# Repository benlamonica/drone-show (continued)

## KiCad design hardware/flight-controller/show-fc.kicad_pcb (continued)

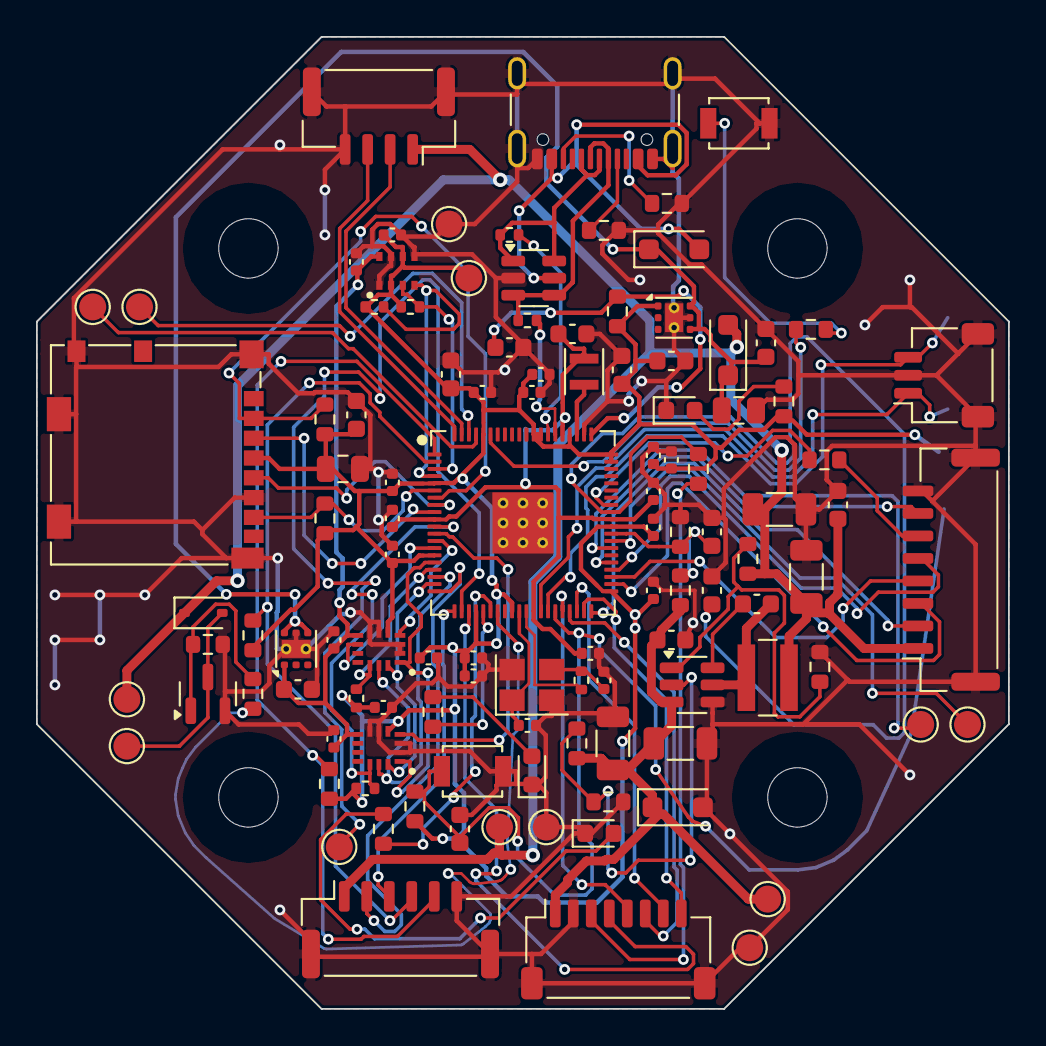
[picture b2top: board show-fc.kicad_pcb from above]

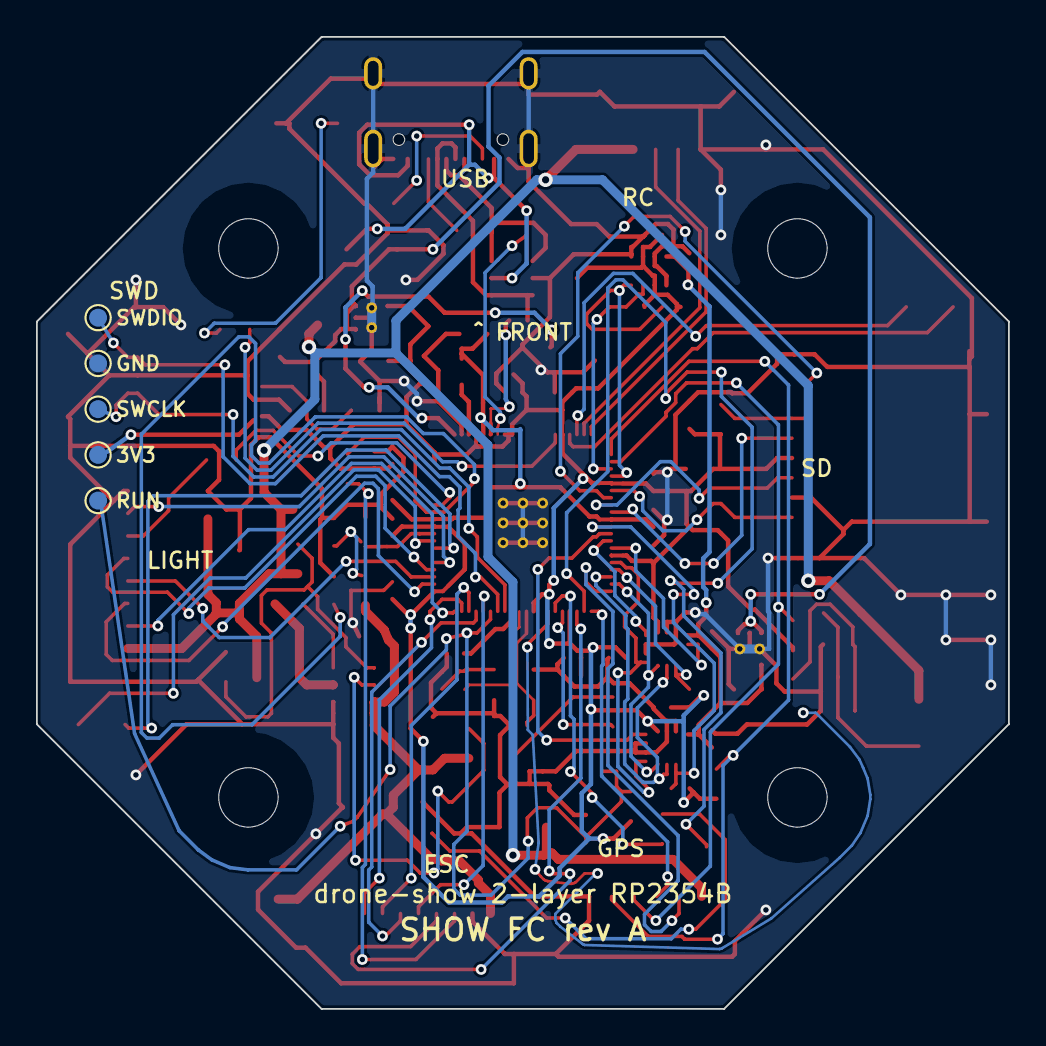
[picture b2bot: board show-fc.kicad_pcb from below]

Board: 2 copper layers, 54.0 x 54.0 mm, 121 parts (5 on the bottom side), 76 nets.

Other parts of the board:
TP14: SWDIO; TestPoint_Pad_D1.0mm
TP15: GND; TestPoint_Pad_D1.0mm
TP16: SWCLK; TestPoint_Pad_D1.0mm
TP17: +3V3; TestPoint_Pad_D1.0mm
TP18: RUN; TestPoint_Pad_D1.0mm

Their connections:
+3V3: TP17.1; also elsewhere on the board
GND: TP15.1; also elsewhere on the board
RUN: TP18.1; also elsewhere on the board
SWCLK: TP16.1; also elsewhere on the board
SWDIO: TP14.1; also elsewhere on the board

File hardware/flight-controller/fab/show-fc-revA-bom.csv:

Item #,Designator,Qty,Manufacturer,Mfg Part #,Description / Value,Package/Footprint,Type,LCSC,Your Instructions / Notes
1,U1,1,Raspberry Pi,RP2354B,RP2354B,QFN-80-1EP_10x10mm_P0.4mm_EP3.4x3.4mm,SMD,C39843328,
2,"C1,C2,C3,C4,C5,C6,C7,C8,C9,C10,C11,C15,C16,C17,C37,C38,C39,C40,C41,C42",20,Murata,GRM155R71C104KA88D,100n,C_0402_1005Metric,SMD,,
3,L1,1,Abracon,AOTA-B201610S3R3-101-T,3.3uH,L_Murata_DFE201610P,SMD,,RP2350 datasheet part; the dot (pin 1) goes to VREG_LX
4,"C12,C13,C14,C18,C30,C31",6,Murata,GRM188R61A475KE15D,4.7u,C_0603_1608Metric,SMD,,
5,R1,1,Yageo,RC0603FR-0733L,33,R_0603_1608Metric,SMD,,
6,Y1,1,Abracon,ABM8-272-T3,12MHz,Crystal_SMD_3225-4Pin_3.2x2.5mm,SMD,C20625731,
7,R2,1,Yageo,RC0402FR-071KL,1k,R_0402_1005Metric,SMD,,
8,"C19,C20",2,Murata,GRM1555C1H150JA01D,15p,C_0402_1005Metric,SMD,,
9,SW1,1,Omron,B3U-1000P,BOOT,SW_SPST_B3U-1000P,SMD,,
10,"R3,R5,R6,R15,R18",5,Yageo,RC0603FR-071KL,1k,R_0603_1608Metric,SMD,,
11,SW2,1,Omron,B3U-1000P,RESET,SW_SPST_B3U-1000P,SMD,,
12,"R4,R17,R26,R27",4,Yageo,RC0603FR-0710KL,10k,R_0603_1608Metric,SMD,,
13,"C21,C25,C28,C33,C34,C44",6,Murata,GCM188R71H104KA57D,100n,C_0603_1608Metric,SMD,,
14,J8,1,JST,SM03B-SRSS-TB(LF)(SN),SWD,JST_SH_SM03B-SRSS-TB_1x03-1MP_P1.00mm_Horizontal,SMD,,
15,D1,1,Wurth Elektronik,150060BS75000,LED blue,LED_0603_1608Metric,SMD,,
16,D2,1,Wurth Elektronik,150060VS75000,LED green,LED_0603_1608Metric,SMD,,
17,J1,1,GCT,USB4105-GF-A,USB-C,USB_C_Receptacle_GCT_USB4105-xx-A_16P_TopMnt_Horizontal,SMD,,
18,"R7,R8",2,Yageo,RC0603FR-075R1KL,5.1k,R_0603_1608Metric,SMD,,
19,"R9,R10",2,Yageo,RC0402FR-0727L,27,R_0402_1005Metric,SMD,,
20,U2,1,STMicroelectronics,USBLC6-2SC6,USBLC6-2SC6,SOT-23-6,SMD,,
21,D3,1,Littelfuse,SMF30A,SMF30A,D_SOD-123F,SMD,,"unidirectional; cathode (pad 1) on VBAT, clamps ESC spikes below the buck's 60 V rating"
22,"C22,C23",2,Murata,GRM31CR61H106KA12L,10u 50V,C_1206_3216Metric,SMD,,
23,C24,1,Murata,GCM188R71H104KA57D,100n 50V,C_0603_1608Metric,SMD,,
24,U3,1,Texas Instruments,LMR51635YDDCR,LMR51635YDDCR,SOT-23-6,SMD,C45262770,
25,"R11,R16,R35",3,Yageo,RC0603FR-07100KL,100k,R_0603_1608Metric,SMD,,
26,R12,1,Yageo,RC0603FR-0714KL,14k,R_0603_1608Metric,SMD,,
27,L2,1,Wurth Elektronik,74438357047,4.7uH,L_Wuerth_MAPI-4020,SMD,,
28,R13,1,Yageo,RC0603FR-0753R6KL,53.6k,R_0603_1608Metric,SMD,,
29,R14,1,Yageo,RC0603FR-0710R2KL,10.2k,R_0603_1608Metric,SMD,,
30,"C26,C27",2,Murata,GRM31CR61E226KE15L,22u 25V,C_1206_3216Metric,SMD,,
31,"D4,D5",2,Nexperia,"PMEG3020EH,115",PMEG3020EH,D_SOD-123F,SMD,,
32,"C29,C43",2,Murata,GRM21BR61C106KE15L,10u,C_0805_2012Metric,SMD,,
33,U4,1,Texas Instruments,LP5912-3.3DRVR,LP5912-3.3DRVR,WSON-6-1EP_2x2mm_P0.65mm_EP1x1.6mm_ThermalVias,SMD,C524780,
34,U5,1,Texas Instruments,LP5912-1.8DRVR,LP5912-1.8DRVR,WSON-6-1EP_2x2mm_P0.65mm_EP1x1.6mm_ThermalVias,SMD,C2876234,clean supply for the IMU and barometer cores
35,C32,1,Murata,GRM188R61E105KA12D,1u,C_0603_1608Metric,SMD,,
36,D6,1,Wurth Elektronik,150060RS75000,LED red,LED_0603_1608Metric,SMD,,
37,U6,1,TDK InvenSense,ICM-42688-P,ICM-42688-P,LGA-14_3x2.5mm_P0.5mm,SMD,,"IMU1; pin 9 is CLKIN, driven by a 32 kHz PWM from GPIO15"
38,U7,1,Bosch Sensortec,BMI270,BMI270,LGA-14_3x2.5mm_P0.5mm,SMD,C2836813,"IMU2, different vendor for redundancy"
39,"R22,R23",2,Yageo,RC0402FR-0710KL,10k,R_0402_1005Metric,SMD,,
40,U8,1,Infineon,DPS368XTSA1,DPS368,Infineon_VLGA-8_2.0x2.5mm_P0.65mm,SMD,,"I2C address 0x76 (SDO low), CSB high selects I2C. Cover with open-cell foam."
41,"R24,R25",2,Yageo,RC0402FR-072R2KL,2.2k,R_0402_1005Metric,SMD,,
42,J2,1,Molex,1040310811,microSD,microSD_HC_Molex_104031-0811,SMD,,
43,J3,1,JST,SM08B-SRSS-TB(LF)(SN),ESC,JST_SH_SM08B-SRSS-TB_1x08-1MP_P1.00mm_Horizontal,SMD,C160407,"Betaflight standard ESC pinout, same as OpenFC-Lite P1"
44,J4,1,JST,SM06B-GHS-TB(LF)(SN),GPS,JST_GH_SM06B-GHS-TB_1x06-1MP_P1.25mm_Horizontal,SMD,,Pixhawk GPS1 pinout: RTK board with compass
45,J5,1,JST,SM08B-GHS-TB(LF)(SN),LIGHT,JST_GH_SM08B-GHS-TB_1x08-1MP_P1.25mm_Horizontal,SMD,,"light / Wi-Fi board: MAVLink UART with flow control, LED data, GPIO"
46,J6,1,JST,SM04B-GHS-TB(LF)(SN),RC,JST_GH_SM04B-GHS-TB_1x04-1MP_P1.25mm_Horizontal,SMD,,CRSF / SBUS receiver for the safety pilot
47,R31,1,Yageo,RC0603FR-0747L,47,R_0603_1608Metric,SMD,,
48,"R32,R33",2,Yageo,RC0603FR-072R2KL,2.2k,R_0603_1608Metric,SMD,,
49,Q1,1,onsemi,2N7002LT1G,2N7002,SOT-23,SMD,,
50,R34,1,Yageo,RC0603FR-07100L,100,R_0603_1608Metric,SMD,,
51,D7,1,onsemi,1N4148WS,1N4148WS,D_SOD-323,SMD,,

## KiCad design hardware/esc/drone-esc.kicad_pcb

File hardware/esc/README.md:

# drone-esc: 4-layer 4-in-1 ESC for the show drones

A 4-layer re-layout of [OpenESC-30x30](https://github.com/benlamonica/OpenESC-30x30)
for PCBWay's standard process. The circuit is the prototype's (four AT32F421
MCUs running AM32, four NSG2065Q gate drivers, 24 SP40N01GHNK FETs, INA186
current sense, LMR54406 10 V buck, TLV767 3.3 V LDO). What changed is the
board: 4 layers instead of 6, 0402 and bigger passives, and an 80 mm octagon
instead of a 30 x 30 mm square.

## Status

The board is placed and routed. KiCad DRC shows 0 errors and 0 unconnected
items. The remaining warnings are expected: schematic parity for U3 pins 3 to
11 (the FC wire pads were taken off the board, and J1 carries those signals),
the schematic's empty LCSC fields, and a few dangling stubs and thin pour
slivers. Look over the gate drive and current-sense routing before ordering a
big batch. Nobody has built one yet.

## Ratings

| | |
|---|---|
| Battery | 4S to 6S (25.2 V max). The FETs are 40 V parts, so leave the prototype's 6S ceiling alone. |
| Current | about 35 A continuous per motor with airflow, limited by 2 oz copper and the FET package. Show flying (hover plus gentle moves) needs a fraction of that. |
| Firmware | AM32 for AT32F421, same pinout as OpenESC-30x30, flashed over the motor signal lines through J1 (AM32 bootloader), or over SWD test points. |
| FC link | JST-SH 8-pin side entry, SM08B-SRSS-TB (Betaflight 4-in-1 order: VBAT, GND, CURR, TLM, M1 to M4; TLM is not connected). |
| Mounting | 30.5 mm M3 pattern, 3.3 mm unplated holes with a 6.9 mm copper-free ring, so it stacks with the FC on rubber standoffs. |

## Board

* 80 mm across the flats, octagonal, 1.6 mm FR4, 4 layers: 2 oz outer,
  1 oz inner. Layer 2 is a solid GND plane; layer 3 is a +BATT pour that a
  few signal tracks also cross.
* Two layers were tried first and did not work: at 66 mm the gate-drive lines
  had no room, and at 74 mm the routing cut the GND pour into islands, which
  is no good on a board switching 100+ A. The inner planes fix both and give a
  much shorter commutation loop.
* Each motor owns one edge. The high-side FET of each half-bridge is on top,
  its low-side FET directly underneath on the bottom, and the phase copper runs
  out to plated motor pads on the edge.
* The outer layers are +BATT pour on top and GND pour on the bottom, stitched
  to the inner planes.
* The motor channels own the four axis edges; the corner flats carry the
  connections:
  * **Battery** on the rear-right corner flat (marked BAT+ / BAT- on both
    sides). Each pad is a 7 x 6 mm plated pad with bare copper on both sides,
    a 2.2 mm hole (12 or 14 AWG goes straight through) and a ring of eight
    small plated holes so the current reaches both sides. Solder the battery
    lead on one side and the low-ESR electrolytic (35 V, 470 uF or more) on
    the other, legs on the matching pads, so the cap sits right at the power
    entry. The two current-sense shunts sit right beside BAT+, with the INA186
    and its input filter underneath on the bottom. Its output filter (R73,
    C94) is at the FC end, under J1.
  * **FC connector** J1 on the front-left corner flat: a side-entry JST SH
    with its opening facing out of the board edge, so the lead leaves sideways
    instead of standing up into the stack.
* Each channel's logic sits on the bottom, on the GND pour, in the wedge
  between the board centre and its FETs. The gate driver is just inboard of
  the FETs, with the gate resistors and bootstrap caps. The MCU is on the
  centre side of the driver, 6 mm from the middle of the board, so the six
  PWM lines are a few millimetres long and stay on one layer. The four MCUs
  form a ring round the centre, with their DShot resistors in the middle.
  The MCU's NRST, BOOT0 and VDDA parts, its 3V3 decoupling cap and the SWD
  test points are on top, right over it. The corners stay free for the
  battery, the FC connector and the 10 V / 3.3 V supplies, which are on the
  bottom of the rear-left corner.
* The MCU and gate-driver pins are 0.4 and 0.5 mm apart and boxed in on
  every side, which neither router gets out of reliably. So the MCU, the
  driver and the caps round them are placed exactly, and the escapes are
  drawn by `tools/route_prep.py`, the same in every channel: the PWM lines,
  the 3V3, NRST, VDDA and back-EMF escapes, and the driver's high-side row.
  The high-side gate lines drop to vias there and cross on top. 0.18 mm
  tracks keep every gap at 0.22 mm or more.
* 24 x 10 uF 1206 ceramics sit around the power path, next to each channel's
  high-side FETs.
* Parts: the MCU passives (decoupling, NRST, BOOT0, VDDA, back-EMF dividers,
  DShot resistor) are 0402, which gives the MCU room for a clear ring of
  escape tracks; everything else is 0603 or bigger. Nothing is smaller than
  0402. The ICs are the prototype's packages; the MCU QFN at 0.4 mm pitch is
  the finest pitch on the board.

### Changes from the prototype BOM

* The prototype's 0201 and 0402 resistors and capacitors became 0402 round
  each MCU (YAGEO RC0402, Samsung CL05B104KB5NNNC) and 0603 everywhere else
  (YAGEO RC0603, Samsung CL10). Same values throughout.
* J1 is the side-entry SM08B-SRSS-TB instead of a top-entry connector.
* The bulk ceramics are now real schematic symbols (C100 to C123) so they are
  in the BOM and the pick-and-place file.
* QFN-28 footprint: the prototype's footprint was missing pads 8, 23 and 24.
  They are back, so every MCU pin is soldered.

## Making it at PCBWay

Upload `fab/drone-esc-gerbers.zip` and choose:

| Option | Value |
|---|---|
| Layers | 4 |
| Material / thickness | FR-4 TG150, 1.6 mm |
| Copper | 2 oz outer, 1 oz inner |
| Min track / space | 7 / 8 mil (0.178 / 0.2 mm) |
| Min hole / via | 0.3 mm drill, 0.66 mm via pad (7 mil ring) |
| Surface finish | ENIG (flat pads for the QFNs) or lead-free HASL |
| Solder mask / silk | any colour |

For assembly upload `fab/drone-esc-bom.csv` and `fab/drone-esc-cpl.csv`.
Parts are on both sides. The design rules PCBWay checks against are in
`drone-esc.kicad_pro` and `drone-esc.kicad_dru`; open the board in KiCad 10 and
run DRC to see them.

## Frame changes this board needs

The board is bigger than the 30x30 prototype, so `frame/frame.py` needs:

* `BODY` 90 to about 110 mm, so the arm sockets clear the board's corner
  flats (37.8 mm from the centre).
* `GPS_MAST_R` 38 to about 53 mm, so the GPS mast clears the board edge
  (40 mm from the centre).
* Check both against the 3D model; they are worked out from the board outline,
  not test-fitted.
* Bottom-side parts stand about 1.2 mm proud of the board. The low ring and
  spokes at boss height in the hub touch them, so either raise the ESC on
  3 mm spacers/grommets or drop the ring by 3 mm.
* The battery leads leave from the rear-right corner flat, where motor 1's arm
  socket is. Leave a gap or notch in the hub wall there for the leads and the
  electrolytic (about 12 mm wide for two 12 AWG leads, more if the cap lies
  beside them), and route the leads back past the arm. The hub floor no longer
  needs a window under the board.
* J1's plug comes out of the front-left corner flat, sideways: leave about
  8 mm clear outside that flat (motor 4's arm socket) for the plug and its
  lead, which then runs up to the FC.

## Notes and limits

* Apart from the drawn escapes, the signal tracks are routed in three steps.
  First `tools/rescue_route.py`, a small grid maze router, routes the MCU's
  short local nets, the bootstrap nets and 3V3 on the near-empty board. Then
  Freerouting routes everything else round them. Finally the maze router
  finishes what Freerouting left open.
* RS2205-class motors are usually wound for 4S. On 6S pick a lower KV
  (about 1700 to 1900 KV) or limit throttle in the FC.
* The FETs and gate drivers sit on both sides, so the board can't be all
  parts-on-top like the FC. Bottom parts stand about 1.2 mm proud; the rubber
  standoffs between stacked boards need to be taller than that. Nothing on the
  board stands up into the stack any more: J1 is side entry and the
  electrolytic hangs off the battery pads.
* Four layers is a bit more per board than two at PCBWay, but still far below
  the prototype's six.

## Rebuilding

Everything is generated by scripts in `tools/` with KiCad 10:

```sh
FREEROUTING=/path/to/freerouting-1.9.0.jar PYTHON=/path/to/venv/bin/python sh tools/build.sh
sh tools/export.sh                                             # board -> fab/
```

A full build takes about 25 minutes on a laptop. `PYTHON` is a plain Python 3 with sexpdata, numpy, scipy and Pillow (the
netlist converter and the rescue router run there); the board scripts run in
KiCad's own Python (`KIPY`, found by itself on macOS). `sh tools/build.sh
place` stops after placement, which takes seconds, for trying placement
changes before a full routing run.

`tools/layout.py` holds the board geometry (size, FET positions, pads) that
the footprint and placement scripts share.

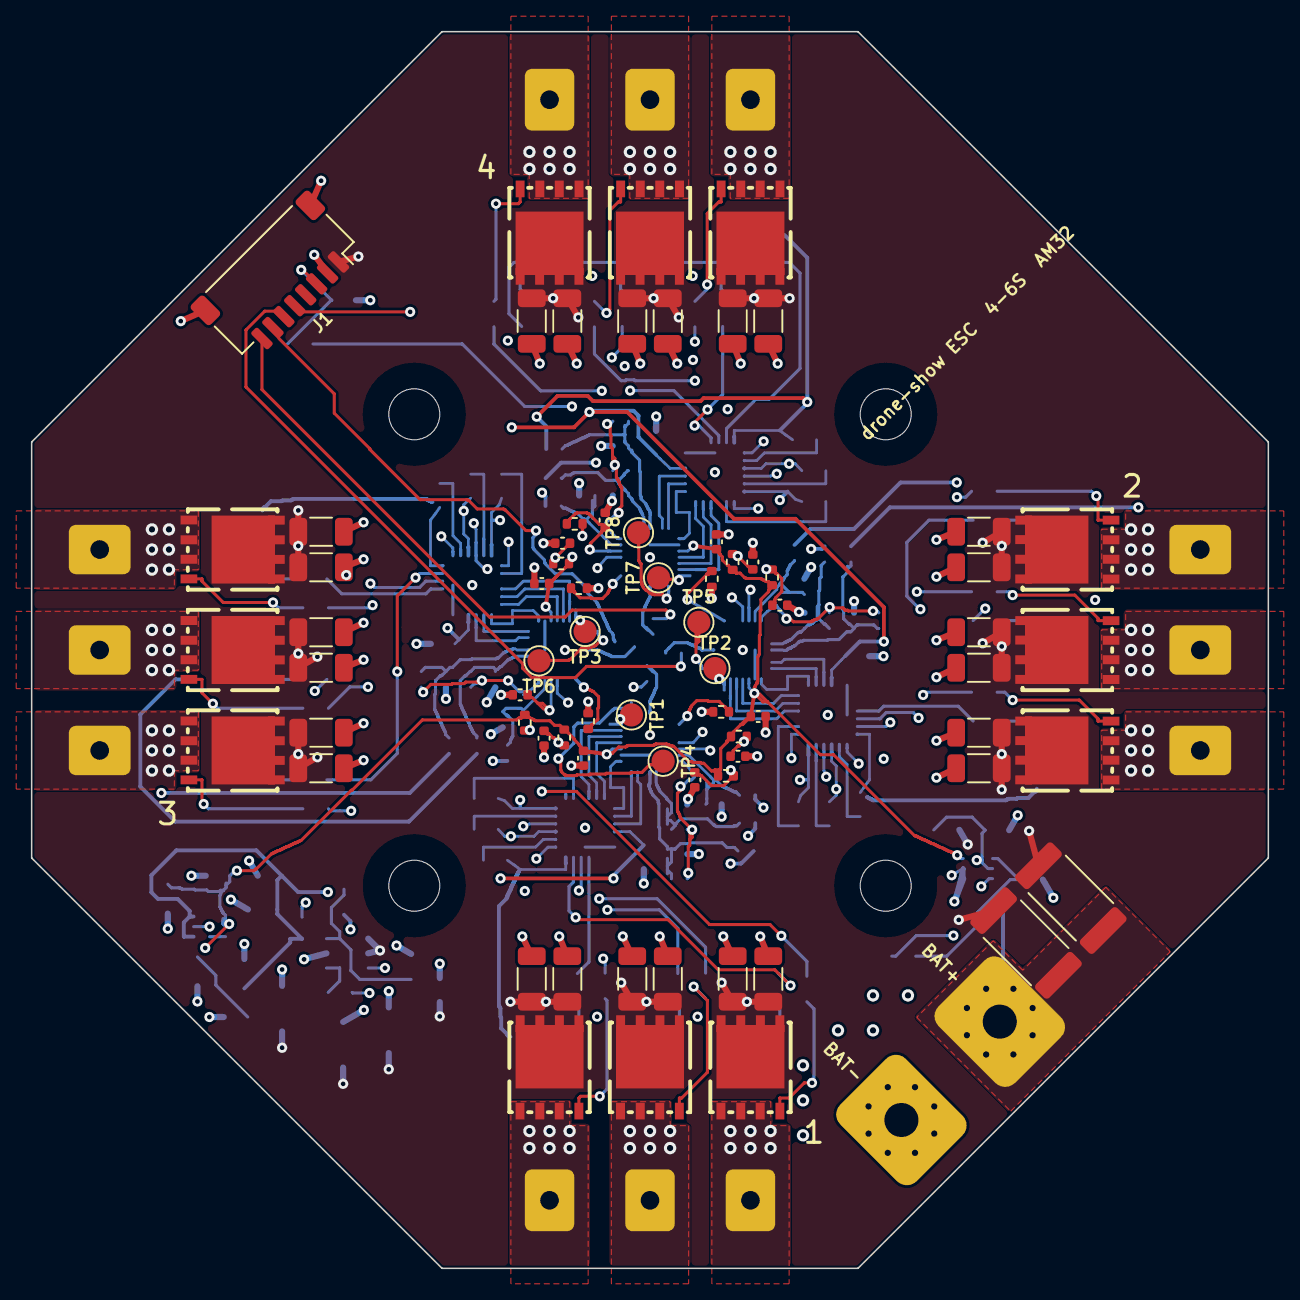
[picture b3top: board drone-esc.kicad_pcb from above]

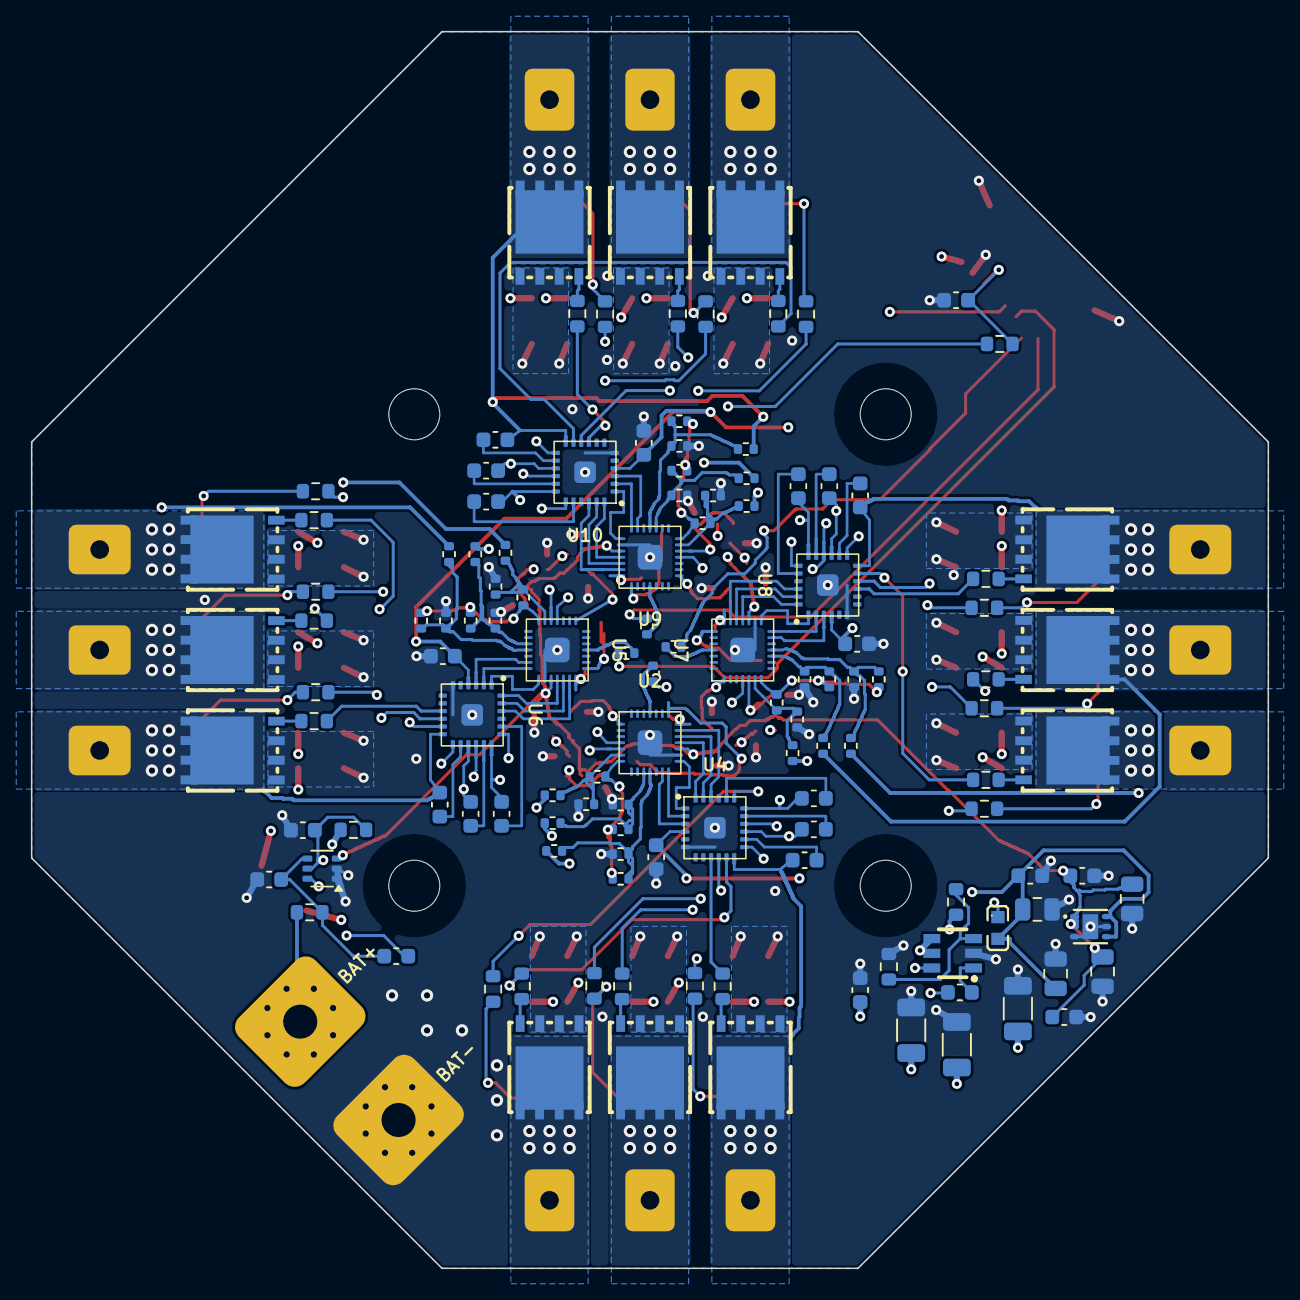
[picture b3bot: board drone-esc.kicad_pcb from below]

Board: 4 copper layers, 80.0 x 80.0 mm, 197 parts (125 on the bottom side), 152 nets.

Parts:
C2, C3, C6: 4.7uF; C_1206_3216Metric
C4, C47, C51, C86: 22uF; C_0805_2012Metric
C32, C33, C34, C35, C36, C37, C38, C39, C40, C41, C53, C56, C57, C58, C62, C63, C67, C68, C74, C75, C76, C81, C93, C94: 100nF; C_0603_1608Metric
C42: 1uF; C_0603_1608Metric
C48, C49, C50, C52, C54, C55, C59, C60, C61, C64, C65, C66: 100nF; C_0402_1005Metric
C100, C101, C102, C103, C104, C105, C106, C107, C108, C109, C110, C111, C112, C113, C114, C115, C116, C117, C118, C119, C120, C121, C122, C123: 10uF; C_1206_3216Metric
J1: SM08B-SRSS-TB; JST_SH_SM08B-SRSS-TB_Horizontal
Q1, Q2, Q3, Q4, Q5, Q6, Q7, Q8, Q9, Q10, Q11, Q12, Q13, Q14, Q15, Q16, Q17, Q18, Q19, Q20, Q21, Q22, Q23, Q24: SP40N01GHNK; PDFN-8L_L6.0-W5.0-P1.27
R10, R12, R13, R15, R18, R19, R21, R22, R25, R27, R28, R30, R31, R33, R34, R36, R40, R41, R46, R48, R49, R51, R52, R54, R58, R59, R64, R66, R67, R69, R70, R72: 10k; R_0402_1005Metric
R11, R14, R26, R29, R32, R35, R47, R50, R53, R65, R68, R71: 1k; R_0402_1005Metric
R20, R39, R57, R87: 220R; R_0402_1005Metric
R23, R24, R37, R38, R42, R43, R44, R45, R55, R56, R60, R61, R62, R63, R74, R75, R76, R77, R78, R79, R80, R81, R82, R83: 15R; R_0603_1608Metric
R73, R89, R90: 1k; R_0603_1608Metric
R84, R85, R86, R88: 10R; R_0402_1005Metric
R120: 115k; R_0603_1608Metric
R121: 10k; R_0603_1608Metric
Rsense1, Rsense2: 0.2mR; R_2512_6332Metric
TP1, TP2, TP3, TP4, TP5, TP6, TP7, TP8: TestPoint; TestPoint_Pad_D1.5mm
U2, U5, U7, U9: AT32F421G8U7; QFN-28_L4.0-W4.0-P0.40-TL-EP2.4
U3: ESC_Pads_Octagon60
U4, U6, U8, U10: NSG2065Q; QFN-24_L4.0-W4.0-P0.50-TL-EP2.8
U12: INA186A3IDCKR; SOT-363_SC-70-6
U13: LMR54406DBVR; SOT-23-6_L2.9-W1.6-P0.95-LS2.8-BR
U14: FTC160808S4R7MBCA; IND-SMD_L1.6-W0.8_FTC160865SR47MBCA
U15: TLV76733DRVR; WSON-6_L2.0-W2.0-P0.65-TL-EP

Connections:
+3V3: C4.2, C49.1, C51.2, C55.1, C61.1, C66.1, C81.1, C93.1, R18.2, R21.2, R40.2, R58.2, R84.2, R85.2, R86.2, R88.2, U2.17, U5.17, U7.17, U9.17, U12.3, U15.1, U15.2
+10V: C47.1, C57.1, C58.1, C63.1, C68.1, C76.1, C86.1, R120.1, U4.4, U6.4, U8.4, U10.4, U14.2, U15.4, U15.6
+BATT: C2.1, C3.1, C6.1, C74.1, C100.1, C101.1, C102.1, C103.1, C104.1, C105.1, C106.1, C107.1, C108.1, C109.1, C110.1, C111.1, C112.1, C113.1, C114.1, C115.1, C116.1, C117.1, C118.1, C119.1, C120.1, C121.1, C122.1, C123.1, J1.1, Q1.3, Q6.3, Q7.3, Q8.3, Q9.3, Q10.3, Q13.3, Q16.3, Q17.3, Q18.3, Q19.3, Q20.3, R89.2, Rsense1.2, Rsense2.2, U13.4, U13.5
/CSA+: R90.2, Rsense1.1, Rsense2.1, U3.1
/CURR: C94.1, J1.3, R73.1
/ESC1/AH: U2.20, U4.22
/ESC1/AL: U2.15, U4.1
/ESC1/BH: U2.19, U4.23
/ESC1/BL: U2.14, U4.2
/ESC1/CH: U2.18, U4.24
/ESC1/CL: U2.13, U4.3
/ESC1/FBA: R25.1, R26.2, R27.2, U2.6
/ESC1/FBB: R28.2, R29.2, R30.2, U2.10
/ESC1/FBC: R31.2, R32.2, R33.2, U2.11
/ESC1/FBCOMMON: R25.2, R28.1, R31.1, U2.7
/ESC1/GHA: R76.1, U4.19
/ESC1/GHB: R55.1, U4.16
/ESC1/GHC: R23.1, U4.13
/ESC1/GLA: R80.1, U4.11
/ESC1/GLB: R62.1, U4.10
/ESC1/GLC: R42.1, U4.9
/ESC1/MotorA: C53.1, Q1.1, Q2.3, R27.1, U3.23, U4.18
/ESC1/MotorB: C32.1, Q6.1, Q11.3, R30.1, U3.22, U4.15
/ESC1/MotorC: C36.1, Q16.1, Q21.3, R33.1, U3.21, U4.12
/ESC1/vdda: C48.1, R84.1, U2.5
/ESC2/AH: U5.20, U6.22
/ESC2/AL: U5.15, U6.1
/ESC2/BH: U5.19, U6.23
/ESC2/BL: U5.14, U6.2
/ESC2/CH: U5.18, U6.24
/ESC2/CL: U5.13, U6.3
/ESC2/FBA: R10.1, R11.2, R12.2, U5.6
/ESC2/FBB: R13.2, R14.2, R15.2, U5.10
/ESC2/FBC: R34.2, R35.2, R36.2, U5.11
/ESC2/FBCOMMON: R10.2, R13.1, R34.1, U5.7
/ESC2/GHA: R77.1, U6.19
/ESC2/GHB: R56.1, U6.16
/ESC2/GHC: R24.1, U6.13
/ESC2/GLA: R81.1, U6.11
/ESC2/GLB: R63.1, U6.10
/ESC2/GLC: R43.1, U6.9
/ESC2/MotorA: C56.1, Q3.3, Q7.1, R12.1, U3.20, U6.18
/ESC2/MotorB: C33.1, Q8.1, Q12.3, R15.1, U3.19, U6.15
/ESC2/MotorC: C37.1, Q17.1, Q22.3, R36.1, U3.18, U6.12
/ESC2/vdda: C54.1, R85.1, U5.5
/ESC3/AH: U7.20, U8.22
/ESC3/AL: U7.15, U8.1
/ESC3/BH: U7.19, U8.23
/ESC3/BL: U7.14, U8.2
/ESC3/CH: U7.18, U8.24
/ESC3/CL: U7.13, U8.3
/ESC3/FBA: R46.1, R47.2, R48.2, U7.6
/ESC3/FBB: R49.2, R50.2, R51.2, U7.10
/ESC3/FBC: R52.2, R53.2, R54.2, U7.11
/ESC3/FBCOMMON: R46.2, R49.1, R52.1, U7.7
/ESC3/GHA: R78.1, U8.19
/ESC3/GHB: R60.1, U8.16
/ESC3/GHC: R37.1, U8.13
/ESC3/GLA: R82.1, U8.11
/ESC3/GLB: R74.1, U8.10
/ESC3/GLC: R44.1, U8.9
/ESC3/MotorA: C62.1, Q4.3, Q13.1, R48.1, U3.15, U8.18
/ESC3/MotorB: C34.1, Q9.1, Q14.3, R51.1, U3.16, U8.15
/ESC3/MotorC: C38.1, Q18.1, Q23.3, R54.1, U3.17, U8.12
/ESC3/vdda: C60.1, R86.1, U7.5
/ESC4/AH: U9.20, U10.22
/ESC4/AL: U9.15, U10.1
/ESC4/BH: U9.19, U10.23
/ESC4/BL: U9.14, U10.2
/ESC4/CH: U9.18, U10.24
/ESC4/CL: U9.13, U10.3
/ESC4/FBA: R64.1, R65.2, R66.2, U9.6
/ESC4/FBB: R67.2, R68.2, R69.2, U9.10
/ESC4/FBC: R70.2, R71.2, R72.2, U9.11
/ESC4/FBCOMMON: R64.2, R67.1, R70.1, U9.7
/ESC4/GHA: R79.1, U10.19
/ESC4/GHB: R61.1, U10.16
/ESC4/GHC: R38.1, U10.13
/ESC4/GLA: R83.1, U10.11
/ESC4/GLB: R75.1, U10.10
/ESC4/GLC: R45.1, U10.9
/ESC4/MotorA: C67.1, Q5.3, Q19.1, R66.1, U3.12, U10.18
/ESC4/MotorB: C35.1, Q10.1, Q15.3, R69.1, U3.13, U10.15
/ESC4/MotorC: C39.1, Q20.1, Q24.3, R72.1, U3.14, U10.12
/ESC4/vdda: C65.1, R88.1, U9.5
/M1: J1.5, R20.1
/M2: J1.6, R39.1
/M3: J1.7, R57.1
/M4: J1.8, R87.1
GND: C2.2, C3.2, C4.1, C6.2, C40.2, C41.2, C47.2, C48.2, C49.2, C50.2, C51.1, C52.2, C54.2, C55.2, C57.2, C58.2, C59.2, C60.2, C61.2, C63.2, C64.2, C65.2, C66.2, C68.2, C74.2, C76.2, C81.2, C86.2, C93.2, C94.2, C100.2, C101.2, C102.2, C103.2, C104.2, C105.2, C106.2, C107.2, C108.2, C109.2, C110.2, C111.2, C112.2, C113.2, C114.2, C115.2, C116.2, C117.2, C118.2, C119.2, C120.2, C121.2, C122.2, C123.2, J1.2, J1.P1, J1.P2, Q2.1, Q3.1, Q4.1, Q5.1, Q11.1, Q12.1, Q14.1, Q15.1, Q21.1, Q22.1, Q23.1, Q24.1, R11.1, R14.1, R19.2, R22.2, R26.1, R29.1, R32.1, R35.1, R41.2, R47.1, R50.1, R53.1, R59.2, R65.1, R68.1, R71.1, R121.2, U2.16, U2.29, U3.2, U4.6, U4.25, U5.16, U5.29, U6.6, U6.25, U7.16, U7.29, U8.6, U8.25, U9.16, U9.29, U10.6, U10.25, U12.1, U12.2, U13.2, U15.3, U15.5, U15.7
unnamed: Q1.2, R76.2
unnamed: Q2.2, R80.2
unnamed: Q3.2, R81.2
unnamed: Q4.2, R82.2
unnamed: Q5.2, R83.2
unnamed: Q6.2, R55.2
unnamed: Q7.2, R77.2
unnamed: Q8.2, R56.2
unnamed: Q9.2, R60.2
unnamed: Q10.2, R61.2
unnamed: Q11.2, R62.2
unnamed: Q12.2, R63.2
unnamed: Q13.2, R78.2
unnamed: Q14.2, R74.2
unnamed: Q15.2, R75.2
unnamed: Q16.2, R23.2
unnamed: Q17.2, R24.2
unnamed: Q18.2, R37.2
unnamed: Q19.2, R79.2
unnamed: Q20.2, R38.2
unnamed: Q21.2, R42.2
unnamed: Q22.2, R43.2
unnamed: Q23.2, R44.2
unnamed: Q24.2, R45.2
unnamed: R19.1, U2.1
unnamed: C50.1, R18.1, U2.4
unnamed: TP1.1, U2.21
unnamed: TP4.1, U2.22
unnamed: R20.2, U2.25
unnamed: C53.2, U4.20
unnamed: C32.2, U4.17
unnamed: C36.2, U4.14
unnamed: R22.1, U5.1
unnamed: C52.1, R21.1, U5.4
unnamed: TP2.1, U5.21
unnamed: TP5.1, U5.22
unnamed: R39.2, U5.25
unnamed: C56.2, U6.20
unnamed: C33.2, U6.17
unnamed: C37.2, U6.14
unnamed: R41.1, U7.1
unnamed: C59.1, R40.1, U7.4
unnamed: TP3.1, U7.21
unnamed: TP6.1, U7.22
unnamed: R57.2, U7.25
unnamed: C62.2, U8.20
unnamed: C34.2, U8.17
unnamed: C38.2, U8.14
unnamed: R59.1, U9.1
unnamed: C64.1, R58.1, U9.4
unnamed: TP7.1, U9.21
unnamed: TP8.1, U9.22
unnamed: R87.2, U9.25
unnamed: C67.2, U10.20
unnamed: C35.2, U10.17
unnamed: C39.2, U10.14
unnamed: C41.1, C42.2, R90.1, U12.4
unnamed: C40.1, C42.1, R89.1, U12.5
unnamed: R73.2, U12.6
unnamed: C75.2, U13.1
unnamed: R120.2, R121.1, U13.3
unnamed: C75.1, U13.6, U14.1

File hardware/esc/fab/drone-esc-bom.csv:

Designator,Qty,Value,Footprint,Manufacturer,MPN,LCSC,Mouser
"C2,C3,C6",3,4.7uF,Capacitor_SMD:C_1206_3216Metric,Murata,GRM31CR71H475KA12L,,
"C4,C47,C51,C86",4,22uF,Capacitor_SMD:C_0805_2012Metric,Samsung,CL21A226MAQNNNE,,
"C32,C33,C34,C35,C36,C37,C38,C39,C40,C41,C53,C56,C57,C58,C62,C63,C67,C68,C74,C75,C76,C81,C93,C94",24,100nF,Capacitor_SMD:C_0603_1608Metric,Samsung,CL10B104KB8NNNC,,
C42,1,1uF,Capacitor_SMD:C_0603_1608Metric,Samsung,CL10B105KB8NNNC,,
"C48,C49,C50,C52,C54,C55,C59,C60,C61,C64,C65,C66",12,100nF,Capacitor_SMD:C_0402_1005Metric,Samsung,CL05B104KB5NNNC,,
"C100,C101,C102,C103,C104,C105,C106,C107,C108,C109,C110,C111,C112,C113,C114,C115,C116,C117,C118,C119,C120,C121,C122,C123",24,10uF,Capacitor_SMD:C_1206_3216Metric,Murata,GRM31CR61H106MA12L,,
J1,1,SM08B-SRSS-TB,drone-esc:JST_SH_SM08B-SRSS-TB_Horizontal,JST,SM08B-SRSS-TB(LF)(SN),C160407,
"Q1,Q2,Q3,Q4,Q5,Q6,Q7,Q8,Q9,Q10,Q11,Q12,Q13,Q14,Q15,Q16,Q17,Q18,Q19,Q20,Q21,Q22,Q23,Q24",24,SP40N01GHNK,drone-esc:PDFN-8L_L6.0-W5.0-P1.27,Siliup,SP40N01GHNK,C22385416,
"R10,R12,R13,R15,R18,R19,R21,R22,R25,R27,R28,R30,R31,R33,R34,R36,R40,R41,R46,R48,R49,R51,R52,R54,R58,R59,R64,R66,R67,R69,R70,R72",32,10k,Resistor_SMD:R_0402_1005Metric,YAGEO,RC0402FR-0710KL,,
"R11,R14,R26,R29,R32,R35,R47,R50,R53,R65,R68,R71",12,1k,Resistor_SMD:R_0402_1005Metric,YAGEO,RC0402FR-071KL,,
"R20,R39,R57,R87",4,220R,Resistor_SMD:R_0402_1005Metric,YAGEO,RC0402FR-07220RL,,
"R23,R24,R37,R38,R42,R43,R44,R45,R55,R56,R60,R61,R62,R63,R74,R75,R76,R77,R78,R79,R80,R81,R82,R83",24,15R,Resistor_SMD:R_0603_1608Metric,YAGEO,RC0603FR-0715RL,,
"R73,R89,R90",3,1k,Resistor_SMD:R_0603_1608Metric,YAGEO,RC0603FR-071KL,,
"R84,R85,R86,R88",4,10R,Resistor_SMD:R_0402_1005Metric,YAGEO,RC0402FR-0710RL,,
R120,1,115k,Resistor_SMD:R_0603_1608Metric,YAGEO,RC0603FR-07115KL,,
R121,1,10k,Resistor_SMD:R_0603_1608Metric,YAGEO,RC0603FR-0710KL,,
"Rsense1,Rsense2",2,0.2mR,Resistor_SMD:R_2512_6332Metric,Yezhan,ASR-S-3-0.2F,C695806,
"U2,U5,U7,U9",4,AT32F421G8U7,drone-esc:QFN-28_L4.0-W4.0-P0.40-TL-EP2.4,ArteryTek,AT32F421G8U7,C2765098,
"U4,U6,U8,U10",4,NSG2065Q,drone-esc:QFN-24_L4.0-W4.0-P0.50-TL-EP2.8,WXNSIC,NSG2065Q,C41414478,
U12,1,INA186A3IDCKR,drone-esc:SOT-363_SC-70-6,Texas Instruments,INA186A3IDCKR,C2058245,
U13,1,LMR54406DBVR,drone-esc:SOT-23-6_L2.9-W1.6-P0.95-LS2.8-BR,Texas Instruments,LMR54406DBVR,C5219316,
U14,1,FTC160808S4R7MBCA,drone-esc:IND-SMD_L1.6-W0.8_FTC160865SR47MBCA,cjiang,FTC160808S4R7MBCA,C46594347,
U15,1,TLV76733DRVR,drone-esc:WSON-6_L2.0-W2.0-P0.65-TL-EP,Texas Instruments,TLV76733DRVR,C2848334,
